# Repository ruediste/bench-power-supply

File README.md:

# DIY Bench Power Supply
Turn your old ATX power supply into a lab bench power supply. This repository contains all design files as well as the website. 

See https://ruediste.github.io/bench-power-supply/ for details.

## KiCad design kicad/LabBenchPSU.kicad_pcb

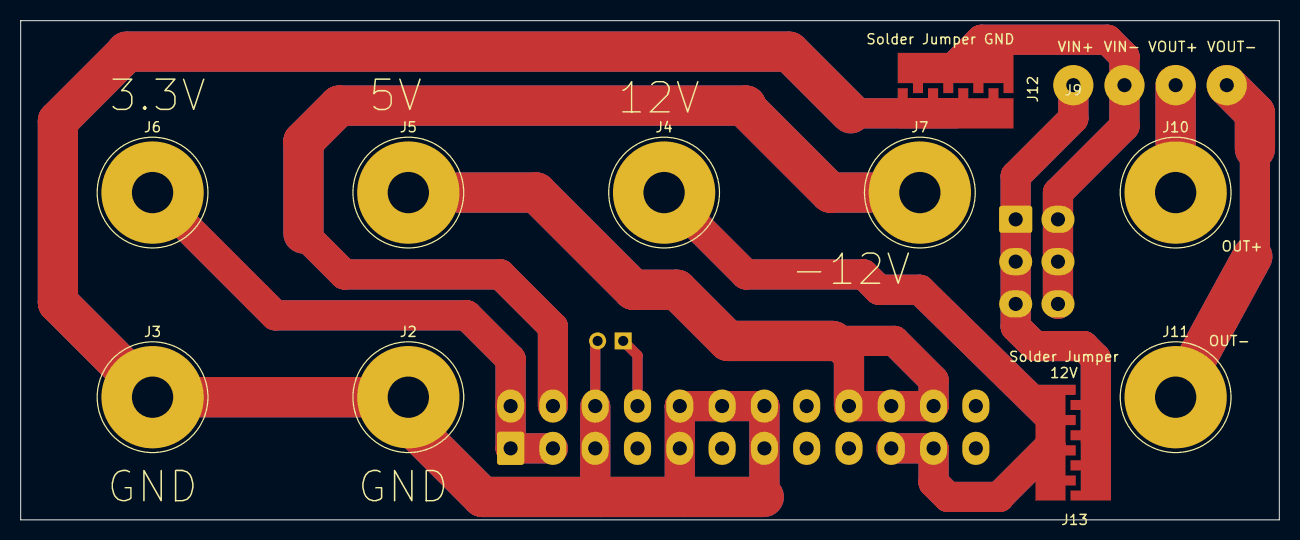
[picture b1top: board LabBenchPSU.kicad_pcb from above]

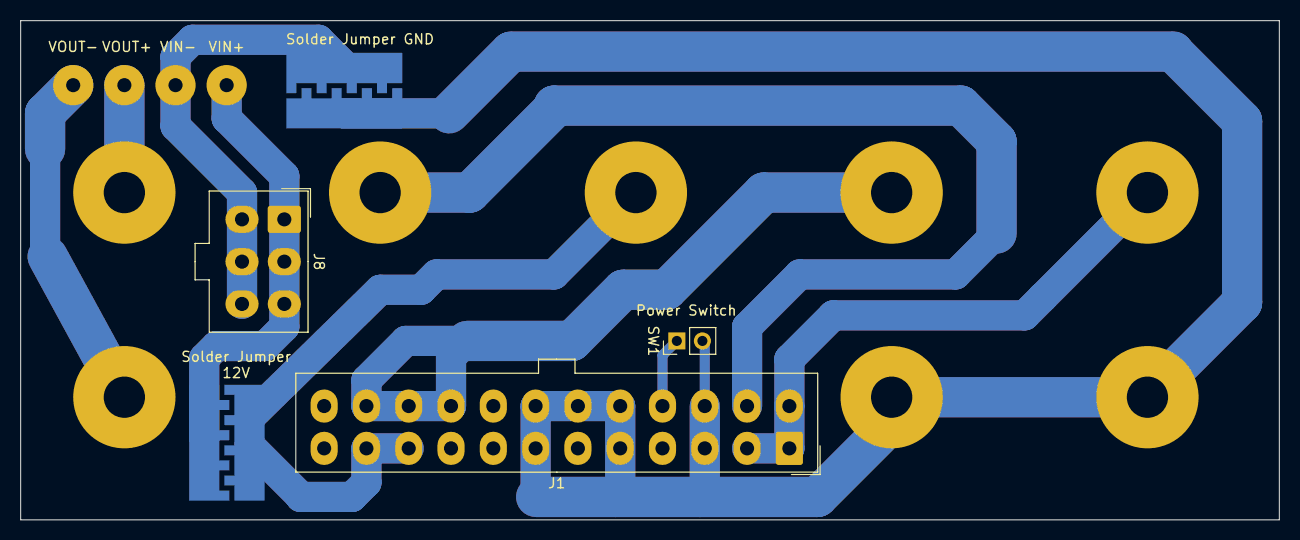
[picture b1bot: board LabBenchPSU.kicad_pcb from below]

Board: 2 copper layers, 125.0 x 49.6 mm, 14 parts (3 on the bottom side), 10 nets.

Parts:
J1: ATX-24; Molex_Mini-Fit_Jr_5566-24A_2x12_P4.20mm_Vertical_4.2mm
J2, J3, J11: GND; Banana_Jack_1Pin_4mm
J4: +12V; Banana_Jack_1Pin_4mm
J5: +5V; Banana_Jack_1Pin_4mm
J6: +3.3V; Banana_Jack_1Pin_4mm
J7: -12V; Banana_Jack_1Pin_4mm
J8: ATX-PCIE; Molex_Mini-Fit_Jr_5566-06A_2x03_P4.20mm_Vertical_4.2mm
J9: DC-DC; Connector High Power 4Pin
J10: V+; Banana_Jack_1Pin_4mm
J12: Solder Gnd; High-Power-Solder-Jumper-Double-Sided
J13: Solder 12V; High-Power-Solder-Jumper-Double-Sided
SW1: PWR; PinHeader_1x02_P2.54mm_Vertical

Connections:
/VIN+: J8.1, J8.2, J8.3, J9.1, J13.2
/VIN-: J8.4, J8.5, J8.6, J9.2, J12.2
/VOUT+: J9.3, J10.1
/VOUT-: J9.4, J11.1
unnamed: J1.1, J1.2, J1.12, J1.13, J6.1
unnamed: J1.10, J1.11, J4.1, J13.1
unnamed: J1.14, J7.1
unnamed: J1.3, J1.5, J1.7, J1.15, J1.17, J1.18, J1.19, J1.24, J2.1, J3.1, J12.1, SW1.2
unnamed: J1.16, SW1.1
unnamed: J1.4, J1.6, J1.21, J1.22, J1.23, J5.1

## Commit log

2021-09-06 move website to correct folder
2021-09-06 disable jekyll
2021-09-07 add affiliate links
2021-09-08 add google analytics
2021-09-10 - remove PCB support from front panel - shorten slot in front panel - reduce wall thickness to 2mm - refactor front panel positioning - add license
2021-09-11 make board double sided
2021-09-16 add german version
2021-09-16 fix language switching on mobile
